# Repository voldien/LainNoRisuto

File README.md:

# LainNoRisuto

Just a collection of electronic schematic and board layouts.

## ARM ToolChain

```bash
```

## AVR ToolChain

```bash
sudo apt-get install gcc-avr binutils-avr avr-libc gdb-avr avrdude
```

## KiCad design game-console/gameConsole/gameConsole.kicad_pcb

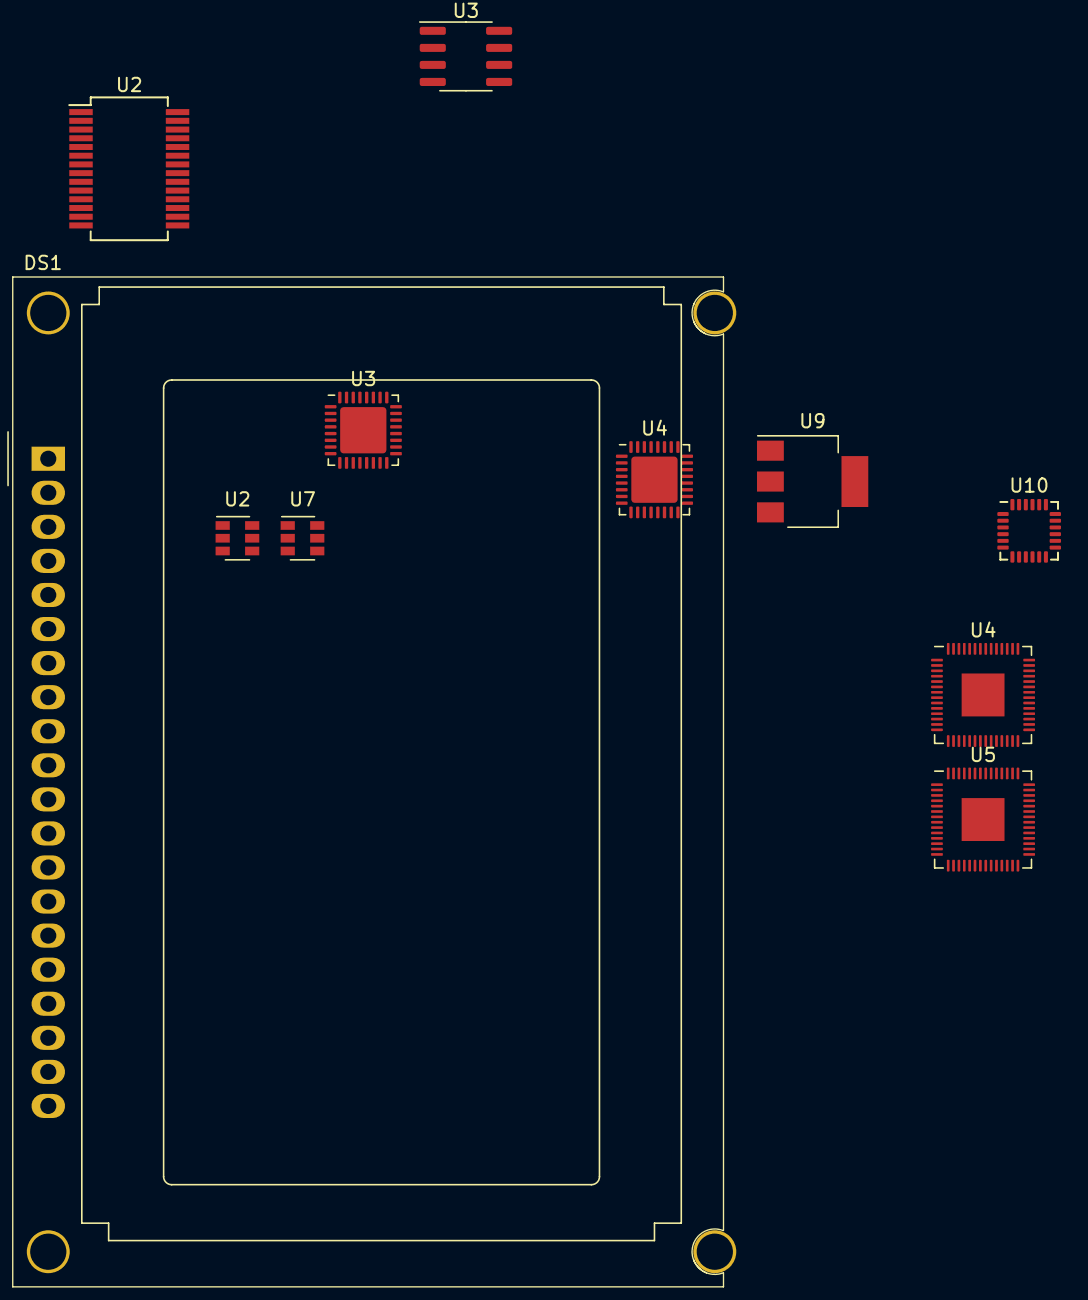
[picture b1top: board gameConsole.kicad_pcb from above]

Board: 2 copper layers, 11 parts (0 on the bottom side), 11 nets, no tracks yet.

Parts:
DS1: AG12864E
U2: AD1855; SSOP-28_5.3x10.2mm_P0.65mm
U2#2, U7: MCP4725xxx-xCH; SOT-23-6
U3, U4: CS43L21; QFN-32-1EP_5x5mm_P0.5mm_EP3.45x3.45mm
U3#2: DS1307Z+; SOIC-8_3.9x4.9mm_P1.27mm
U4#2, U5: RP2040; QFN-56-1EP_7x7mm_P0.4mm_EP3.2x3.2mm
U9: AP1117-33; SOT-223-3_TabPin2
U10: MPU-6050; InvenSense_QFN-24_4x4mm_P0.5mm

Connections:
+3.3V: U2#2.3 (VDD), U7.3 (VDD), U7.6 (A0), U10.13 (VDD)
GND: U2#2.2 (VSS), U2#2.6 (A0), U3#2.4 (GND), U7.2 (VSS), U10.18 (GND)
unnamed: U2.11, U2.15
unnamed: U3.13, U3.33
unnamed: U4#2.23 (DVDD), U4#2.50 (DVDD)
unnamed: U4#2.1 (IOVDD), U4#2.10 (IOVDD), U4#2.22 (IOVDD), U4#2.33 (IOVDD), U4#2.42 (IOVDD), U4#2.49 (IOVDD)
unnamed: U4.13, U4.33
unnamed: U5.23 (DVDD), U5.50 (DVDD)
unnamed: U5.1 (IOVDD), U5.10 (IOVDD), U5.22 (IOVDD), U5.33 (IOVDD), U5.42 (IOVDD), U5.49 (IOVDD)
SCL: U2#2.5 (SCL), U3#2.6 (SCL), U10.23 (SCL)
SDA: U2#2.4 (SDA), U3#2.5 (SDA), U10.24 (SDA)

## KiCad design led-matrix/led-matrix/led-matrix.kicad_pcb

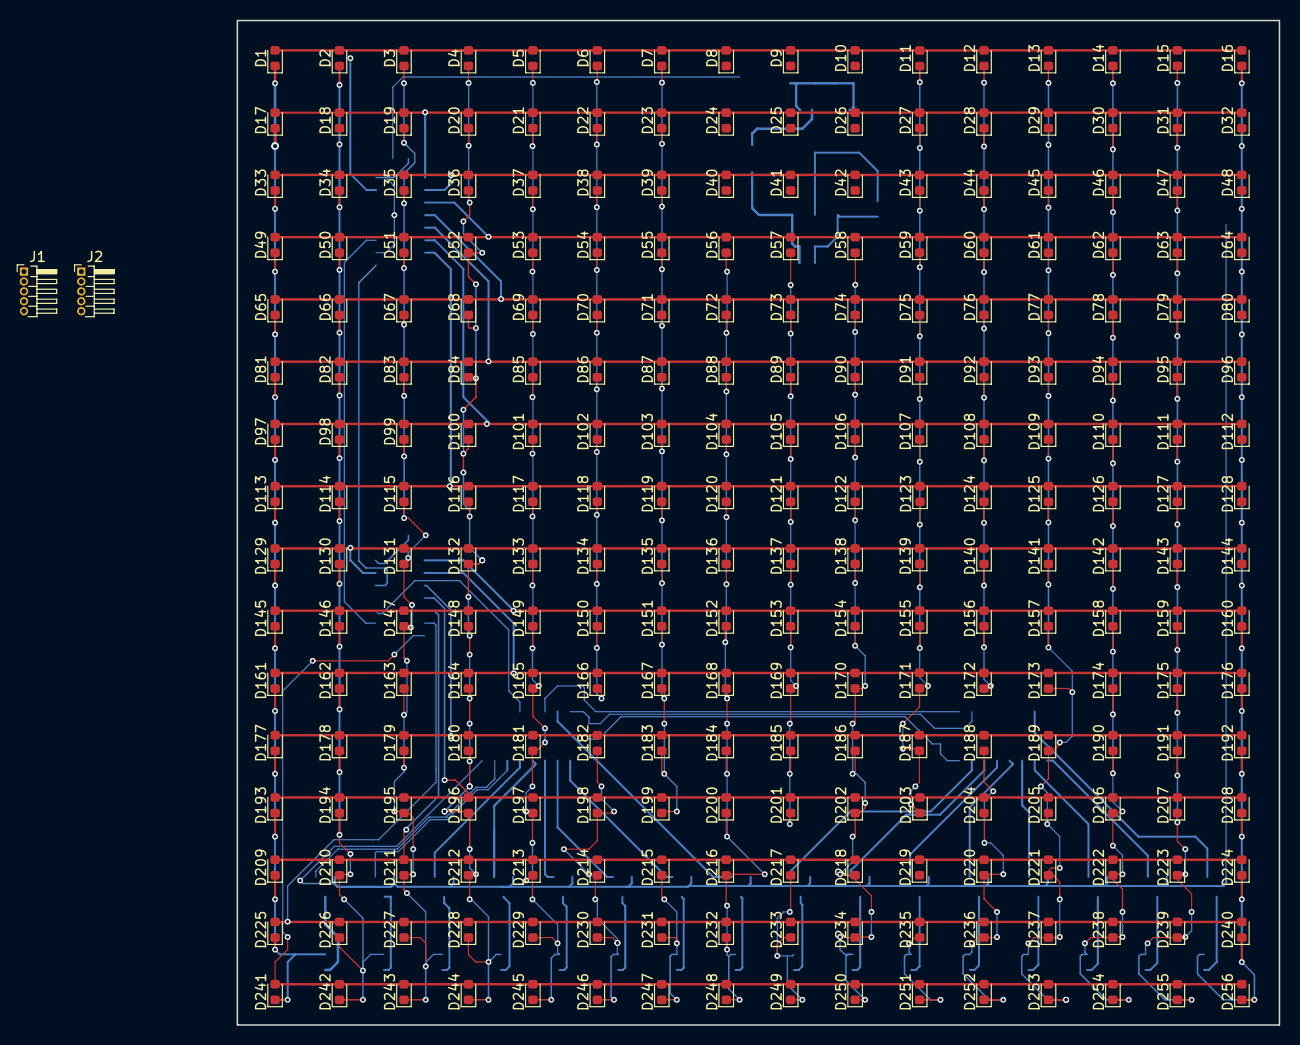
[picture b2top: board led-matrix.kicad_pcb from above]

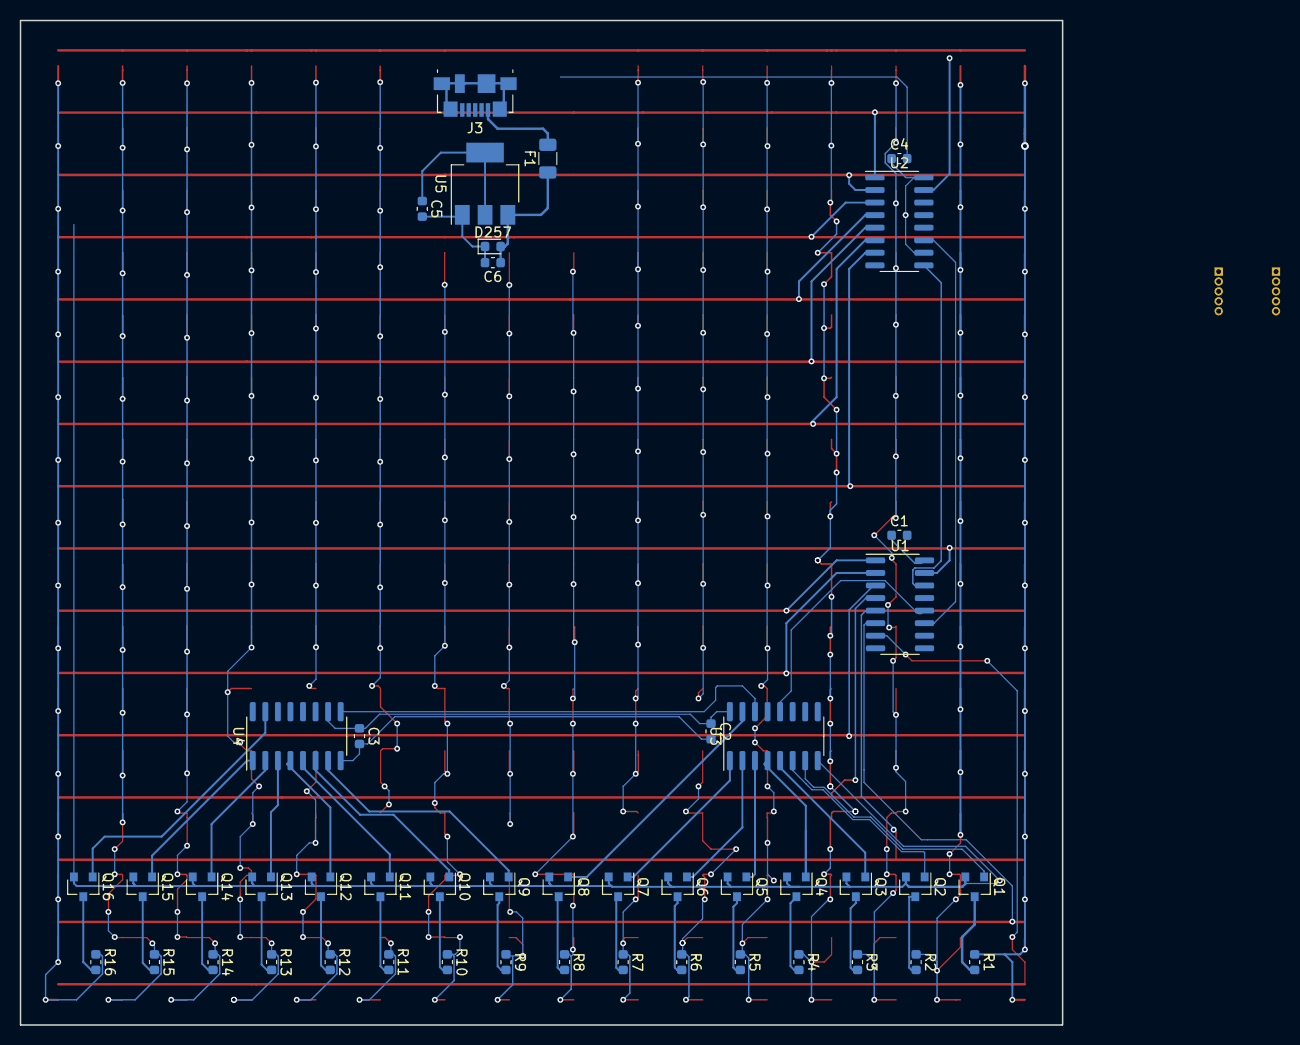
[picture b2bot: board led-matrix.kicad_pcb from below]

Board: 2 copper layers, 105.4 x 101.6 mm, 304 parts (46 on the bottom side), 77 nets.

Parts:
C1, C2, C3, C4, C5, C6: C; C_0603_1608Metric
D1, D2, D3, D4, D5, D6, D7, D8, D9, D10, D11, D12, D13, D14, D15, D16, D17, D18, D19, D20, D21, D22, D23, D24, D25, D26, D27, D28, D29, D30, D31, D32, D33, D34, D35, D36, D37, D38, D39, D40, D41, D42, D43, D44, D45, D46, D47, D48, D49, D50, D51, D52, D53, D54, D55, D56, D57, D58, D59, D60, D61, D62, D63, D64, D65, D66, D67, D68, D69, D70, D71, D72, D73, D74, D75, D76, D77, D78, D79, D80, D81, D82, D83, D84, D85, D86, D87, D88, D89, D90, D91, D92, D93, D94, D95, D96, D97, D98, D99, D100, D101, D102, D103, D104, D105, D106, D107, D108, D109, D110, D111, D112, D113, D114, D115, D116, D117, D118, D119, D120, D121, D122, D123, D124, D125, D126, D127, D128, D129, D130, D131, D132, D133, D134, D135, D136, D137, D138, D139, D140, D141, D142, D143, D144, D145, D146, D147, D148, D149, D150, D151, D152, D153, D154, D155, D156, D157, D158, D159, D160, D161, D162, D163, D164, D165, D166, D167, D168, D169, D170, D171, D172, D173, D174, D175, D176, D177, D178, D179, D180, D181, D182, D183, D184, D185, D186, D187, D188, D189, D190, D191, D192, D193, D194, D195, D196, D197, D198, D199, D200, D201, D202, D203, D204, D205, D206, D207, D208, D209, D210, D211, D212, D213, D214, D215, D216, D217, D218, D219, D220, D221, D222, D223, D224, D225, D226, D227, D228, D229, D230, D231, D232, D233, D234, D235, D236, D237, D238, D239, D240, D241, D242, D243, D244, D245, D246, D247, D248, D249, D250, D251, D252, D253, D254, D255, D256: LED; LED_0603_1608Metric
D257: D_Zener; D_0603_1608Metric
F1: Polyfuse; Fuse_1206_3216Metric
J1, J2: Conn_2Rows-05Pins; PinHeader_1x05_P1.00mm_Horizontal
J3: USB_B_Micro; USB_Micro-B_Molex_47346-0001
Q1, Q2, Q3, Q4, Q5, Q6, Q7, Q8, Q9, Q10, Q11, Q12, Q13, Q14, Q15, Q16: 2N7002; SOT-23
R1, R2, R3, R4, R5, R6, R7, R8, R9, R10, R11, R12, R13, R14, R15, R16: R_US; R_0603_1608Metric
U1, U2, U3, U4: 74LS595; SOIC-16_3.9x9.9mm_P1.27mm
U5: AMS1117-3.3; SOT-223-3_TabPin2

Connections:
+5V: F1.2, J3.1
CLR: J1.4, J2.4, U1.12, U2.12, U3.12, U4.12
COL0: Q16.1, U4.15
COL1: Q15.1, U4.1
COL2: Q14.1, U4.2
COL3: Q13.1, U4.3
COL4: Q12.1, U4.4
COL5: Q11.1, U4.5
COL6: Q10.1, U4.6
COL7: Q9.1, U4.7
COL8: Q8.1, U3.15
COL9: Q7.1, U3.1
COL10: Q6.1, U3.2
COL11: Q5.1, U3.3
COL12: Q4.1, U3.4
COL13: Q3.1, U3.5
COL14: Q2.1, U3.6
COL15: Q1.1, U3.7
COLNEXT: J1.1, U3.9
COLSEQ: U3.14, U4.9
DRIVE0: Q16.3, R16.2
DRIVE1: Q15.3, R15.2
DRIVE2: Q14.3, R14.2
DRIVE3: Q13.3, R13.2
DRIVE4: Q12.3, R12.2
DRIVE5: Q11.3, R11.2
DRIVE6: Q10.3, R10.2
DRIVE7: Q9.3, R9.2
DRIVE8: Q8.3, R8.2
DRIVE9: Q7.3, R7.2
DRIVE10: Q6.3, R6.2
DRIVE11: Q5.3, R5.2
DRIVE12: Q4.3, R4.2
DRIVE13: Q3.3, R3.2
DRIVE14: Q2.3, R2.2
DRIVE15: Q1.3, R1.2
GND: C1.2, C2.2, C3.2, C4.2, C5.2, C6.2, D257.1, J3.5, Q1.2, Q2.2, Q3.2, Q4.2, Q5.2, Q6.2, Q7.2, Q8.2, Q9.2, Q10.2, Q11.2, Q12.2, Q13.2, Q14.2, Q15.2, Q16.2, U1.8, U2.8, U3.8, U4.8, U5.1
unnamed: C6.1, D257.2, F1.1, U5.3
unnamed: D1.1, D17.1, D33.1, D49.1, D65.1, D81.1, D97.1, D113.1, D129.1, D145.1, D161.1, D177.1, D193.1, D209.1, D225.1, D241.1, R1.1
unnamed: D10.1, D26.1, D42.1, D58.1, D74.1, D90.1, D106.1, D122.1, D138.1, D154.1, D170.1, D186.1, D202.1, D218.1, D234.1, D250.1, R10.1
unnamed: D4.1, D20.1, D36.1, D52.1, D68.1, D84.1, D100.1, D116.1, D132.1, D148.1, D164.1, D180.1, D196.1, D212.1, D228.1, D244.1, R4.1
unnamed: D5.1, D21.1, D37.1, D53.1, D69.1, D85.1, D101.1, D117.1, D133.1, D149.1, D165.1, D181.1, D197.1, D213.1, D229.1, D245.1, R5.1
unnamed: D6.1, D22.1, D38.1, D54.1, D70.1, D86.1, D102.1, D118.1, D134.1, D150.1, D166.1, D182.1, D198.1, D214.1, D230.1, D246.1, R6.1
unnamed: D7.1, D23.1, D39.1, D55.1, D71.1, D87.1, D103.1, D119.1, D135.1, D151.1, D167.1, D183.1, D199.1, D215.1, D231.1, D247.1, R7.1
unnamed: D8.1, D24.1, D40.1, D56.1, D72.1, D88.1, D104.1, D120.1, D136.1, D152.1, D168.1, D184.1, D200.1, D216.1, D232.1, D248.1, R8.1
unnamed: D9.1, D25.1, D41.1, D57.1, D73.1, D89.1, D105.1, D121.1, D137.1, D153.1, D169.1, D185.1, D201.1, D217.1, D233.1, D249.1, R9.1
unnamed: D11.1, D27.1, D43.1, D59.1, D75.1, D91.1, D107.1, D123.1, D139.1, D155.1, D171.1, D187.1, D203.1, D219.1, D235.1, D251.1, R11.1
unnamed: D12.1, D28.1, D44.1, D60.1, D76.1, D92.1, D108.1, D124.1, D140.1, D156.1, D172.1, D188.1, D204.1, D220.1, D236.1, D252.1, R12.1
unnamed: D13.1, D29.1, D45.1, D61.1, D77.1, D93.1, D109.1, D125.1, D141.1, D157.1, D173.1, D189.1, D205.1, D221.1, D237.1, D253.1, R13.1
unnamed: D14.1, D30.1, D46.1, D62.1, D78.1, D94.1, D110.1, D126.1, D142.1, D158.1, D174.1, D190.1, D206.1, D222.1, D238.1, D254.1, R14.1
unnamed: D15.1, D31.1, D47.1, D63.1, D79.1, D95.1, D111.1, D127.1, D143.1, D159.1, D175.1, D191.1, D207.1, D223.1, D239.1, D255.1, R15.1
unnamed: D16.1, D32.1, D48.1, D64.1, D80.1, D96.1, D112.1, D128.1, D144.1, D160.1, D176.1, D192.1, D208.1, D224.1, D240.1, D256.1, R16.1
unnamed: D2.1, D18.1, D34.1, D50.1, D66.1, D82.1, D98.1, D114.1, D130.1, D146.1, D162.1, D178.1, D194.1, D210.1, D226.1, D242.1, R2.1
unnamed: D3.1, D19.1, D35.1, D51.1, D67.1, D83.1, D99.1, D115.1, D131.1, D147.1, D163.1, D179.1, D195.1, D211.1, D227.1, D243.1, R3.1
OE: J1.2, J2.2, U1.13, U2.13, U3.13, U4.13
ROW0: D1.2, D2.2, D3.2, D4.2, D5.2, D6.2, D7.2, D8.2, D9.2, D10.2, D11.2, D12.2, D13.2, D14.2, D15.2, D16.2, U2.15
ROW1: D17.2, D18.2, D19.2, D20.2, D21.2, D22.2, D23.2, D24.2, D25.2, D26.2, D27.2, D28.2, D29.2, D30.2, D31.2, D32.2, U2.1
ROW2: D33.2, D34.2, D35.2, D36.2, D37.2, D38.2, D39.2, D40.2, D41.2, D42.2, D43.2, D44.2, D45.2, D46.2, D47.2, D48.2, U2.2
ROW3: D49.2, D50.2, D51.2, D52.2, D53.2, D54.2, D55.2, D56.2, D57.2, D58.2, D59.2, D60.2, D61.2, D62.2, D63.2, D64.2, U2.3
ROW4: D65.2, D66.2, D67.2, D68.2, D69.2, D70.2, D71.2, D72.2, D73.2, D74.2, D75.2, D76.2, D77.2, D78.2, D79.2, D80.2, U2.4
ROW5: D81.2, D82.2, D83.2, D84.2, D85.2, D86.2, D87.2, D88.2, D89.2, D90.2, D91.2, D92.2, D93.2, D94.2, D95.2, D96.2, U2.5
ROW6: D97.2, D98.2, D99.2, D100.2, D101.2, D102.2, D103.2, D104.2, D105.2, D106.2, D107.2, D108.2, D109.2, D110.2, D111.2, D112.2, U2.6
ROW7: D113.2, D114.2, D115.2, D116.2, D117.2, D118.2, D119.2, D120.2, D121.2, D122.2, D123.2, D124.2, D125.2, D126.2, D127.2, D128.2, U2.7
ROW8: D129.2, D130.2, D131.2, D132.2, D133.2, D134.2, D135.2, D136.2, D137.2, D138.2, D139.2, D140.2, D141.2, D142.2, D143.2, D144.2, U1.15
ROW9: D145.2, D146.2, D147.2, D148.2, D149.2, D150.2, D151.2, D152.2, D153.2, D154.2, D155.2, D156.2, D157.2, D158.2, D159.2, D160.2, U1.1
ROW10: D161.2, D162.2, D163.2, D164.2, D165.2, D166.2, D167.2, D168.2, D169.2, D170.2, D171.2, D172.2, D173.2, D174.2, D175.2, D176.2, U1.2
ROW11: D177.2, D178.2, D179.2, D180.2, D181.2, D182.2, D183.2, D184.2, D185.2, D186.2, D187.2, D188.2, D189.2, D190.2, D191.2, D192.2, U1.3
ROW12: D193.2, D194.2, D195.2, D196.2, D197.2, D198.2, D199.2, D200.2, D201.2, D202.2, D203.2, D204.2, D205.2, D206.2, D207.2, D208.2, U1.4
ROW13: D209.2, D210.2, D211.2, D212.2, D213.2, D214.2, D215.2, D216.2, D217.2, D218.2, D219.2, D220.2, D221.2, D222.2, D223.2, D224.2, U1.5
ROW14: D225.2, D226.2, D227.2, D228.2, D229.2, D230.2, D231.2, D232.2, D233.2, D234.2, D235.2, D236.2, D237.2, D238.2, D239.2, D240.2, U1.6
ROW15: D241.2, D242.2, D243.2, D244.2, D245.2, D246.2, D247.2, D248.2, D249.2, D250.2, D251.2, D252.2, D253.2, D254.2, D255.2, D256.2, U1.7
ROWNEXT: J1.3, U1.9
ROWSEQ: U1.14, U2.9
SCK: J1.5, J2.5, U1.11, U2.11, U3.11, U4.11
SERCOL: J2.1, U4.14
SERROW: J2.3, U2.14
VCC: C1.1, C2.1, C3.1, C4.1, C5.1, U1.10, U1.16, U2.10, U2.16, U3.10, U3.16, U4.10, U4.16, U5.2

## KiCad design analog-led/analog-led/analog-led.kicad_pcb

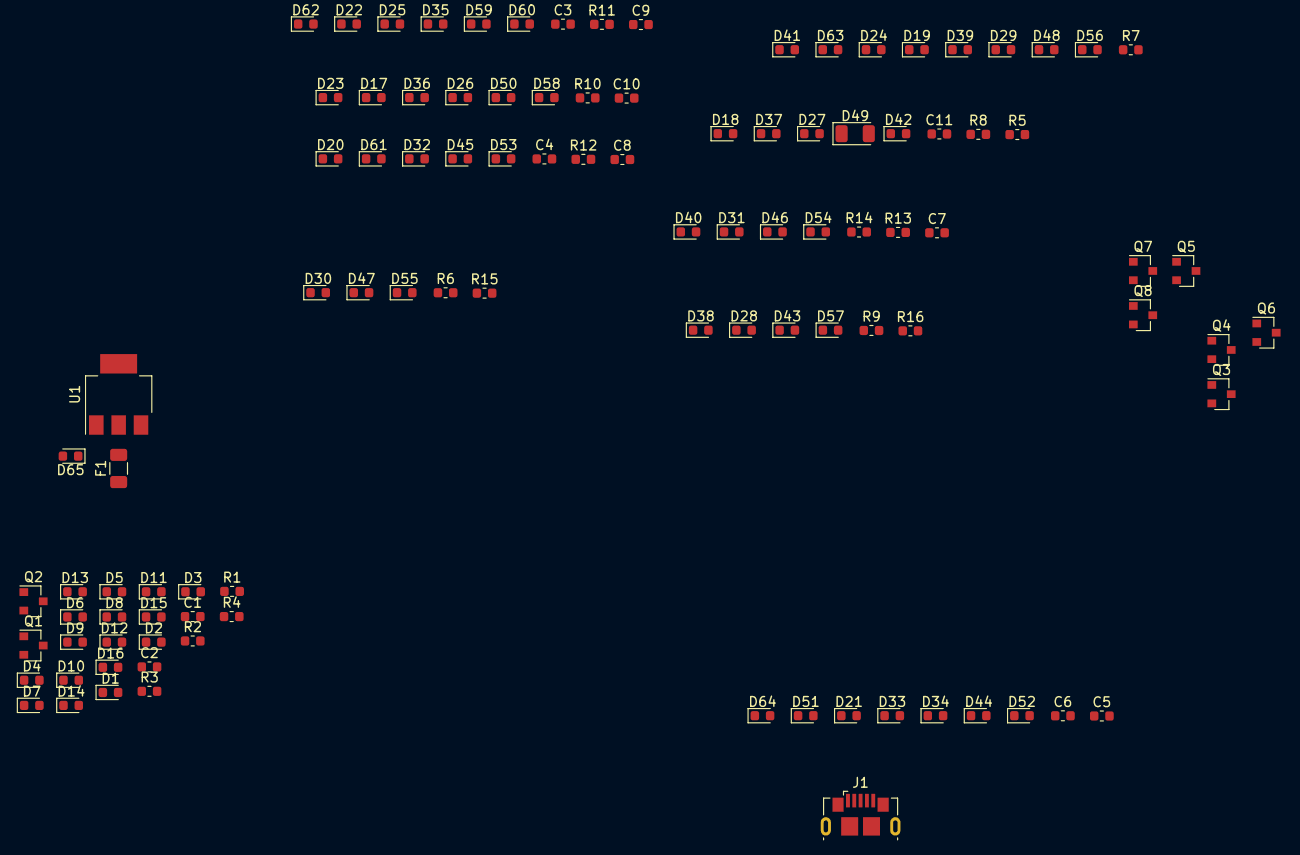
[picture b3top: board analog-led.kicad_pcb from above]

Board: 2 copper layers, 103 parts (0 on the bottom side), 28 nets, no tracks yet.

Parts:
C1, C2, C3, C4, C5, C6, C7, C8, C9, C10, C11: C_Small; C_0603_1608Metric
D1, D2, D3, D4, D5, D6, D7, D8, D9, D10, D11, D12, D13, D14, D15, D16, D17, D18, D19, D20, D21, D22, D23, D24, D25, D26, D27, D28, D29, D30, D31, D32, D33, D34, D35, D36, D37, D38, D39, D40, D41, D42, D43, D44, D45, D46, D47, D48, D50, D51, D52, D53, D54, D55, D56, D57, D58, D59, D60, D61, D62, D63, D64: LED; D_0603_1608Metric
D49: LED; D_1206_3216Metric
D65: D_Zener; D_0603_1608Metric
F1: Fuse; Fuse_1206_3216Metric
J1: USB_B_Micro; USB_Micro-B_GCT_USB3076-30-A
Q1, Q2, Q3, Q4, Q5, Q6, Q7, Q8: BC547; SOT-23
R1, R2, R3, R4, R5, R6, R7, R8, R9, R10, R11, R12, R13, R15, R16: R_Small_US; R_0603_1608Metric
R14: 22K; R_0603_1608Metric
U1: AZ1117-3.3; SOT-223

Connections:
+3V3: C9.2, C10.2, Q1.2, R1.1, R2.1, R3.1, R4.1, R5.1, R6.1, R7.1, R8.1, R9.1, R10.1, R11.1, R12.1, R13.1, R14.1, R15.1, R16.1, U1.3
+5V: F1.1, J1.1
GND: C9.1, C10.1, C11.1, D65.2, J1.5, Q1.3, Q2.3, Q3.3, Q4.3, Q5.3, Q6.3, Q7.3, Q8.3, U1.1
unnamed: C1.1, D1.1, D2.1, D3.1, D4.1, D5.1, D6.1, D7.1, D8.1, Q1.1
unnamed: C1.2, Q2.2, R2.2
unnamed: C2.1, D9.1, D10.1, D11.1, D12.1, D13.1, D14.1, D15.1, D16.1, Q2.1
unnamed: C2.2, Q3.2, R4.2
unnamed: C3.1, D17.1, D18.1, D19.1, D20.1, D21.1, D22.1, D23.1, D24.1, Q3.1
unnamed: C3.2, Q4.2, R6.2
unnamed: C4.1, D25.1, D26.1, D27.1, D28.1, D29.1, D30.1, D31.1, D32.1, Q4.1
unnamed: C4.2, Q5.2, R8.2
unnamed: C5.1, D33.1, D34.1, D35.1, D36.1, D37.1, D38.1, D39.1, D40.1, Q5.1
unnamed: C5.2, Q6.2, R10.2
unnamed: C6.1, D41.1, D42.1, D43.1, D44.1, D45.1, D46.1, D47.1, D48.1, Q6.1
unnamed: C6.2, Q7.2, R12.2
unnamed: C7.1, D49.1, D50.1, D51.1, D52.1, D53.1, D54.1, D55.1, D56.1, Q7.1
unnamed: C7.2, Q8.2, R14.2
unnamed: C8.1, D57.1, D58.1, D59.1, D60.1, D61.1, D62.1, D63.1, D64.1, Q8.1
unnamed: C8.2, R16.2
unnamed: C11.2, D65.1, F1.2, U1.2
unnamed: D1.2, D2.2, D3.2, D4.2, D5.2, D6.2, D7.2, D8.2, R1.2
unnamed: D9.2, D10.2, D11.2, D12.2, D13.2, D14.2, D15.2, D16.2, R3.2
unnamed: D17.2, D18.2, D19.2, D20.2, D21.2, D22.2, D23.2, D24.2, R5.2
unnamed: D25.2, D26.2, D27.2, D28.2, D29.2, D30.2, D31.2, D32.2, R7.2
unnamed: D33.2, D34.2, D35.2, D36.2, D37.2, D38.2, D39.2, D40.2, R9.2
unnamed: D41.2, D42.2, D43.2, D44.2, D45.2, D46.2, D47.2, D48.2, R11.2
unnamed: D49.2, D50.2, D51.2, D52.2, D53.2, D54.2, D55.2, D56.2, R13.2
unnamed: D57.2, D58.2, D59.2, D60.2, D61.2, D62.2, D63.2, D64.2, R15.2

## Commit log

2021-05-01 Config files
2021-05-01 Added tiny blink init source code
2021-05-01 Added init christmas card source code
2021-05-01 Added christmas schematic and pcb board
2021-05-01 Added atdb
2021-05-01 atdb pcb and schematic
2021-05-01 Added schematic and board
2021-05-01 Added root cmake
2021-05-01 Added
2021-05-01 Added readme and license file
2021-05-01 Add more source files
2021-05-01 Addded cmake module for handle avr-gcc with CMake
2021-05-01 Added gerber files
2021-05-01 Added schematic and board layout
2021-05-01 Added image of atdb
2021-05-02 Added layout
2021-05-03 Clock init souce files
2021-05-03 init source files
2021-05-12 Added board layout
2021-05-12 Minor update
2021-05-12 Init readme
2021-08-14 Minor
2021-08-31 Added init LED matrix
2021-09-01 Updated schematic
2021-09-03 Improved annotations and board layout
2021-09-04 Updated layout
2021-09-04 Updated layout grid
2021-09-04 Setup LED matrix
2021-09-05 Updated schematic and layout
2021-09-17 Updated minor
2021-12-22 Init
2022-01-06 Improved layout and schematic
2022-01-06 Init game console design
2022-04-12 Code formated
2023-01-20 Added init christmas card version 2.0
2023-04-06 Added init christmas card version 2 schematic and layout
2023-04-06 removed, replaced
2023-04-06 Added init source code, copied from the christmas card V1
2023-04-06 Added init source code for LED Clock matrix
2023-04-07 Added readme and removed file
2023-05-29 Added kicad git ignore
2023-05-29 Added init kicad source files
2023-05-29 Added init WIP game console firmware code
2023-05-30 Minor improvements
2025-05-21 Improved logic and other changes
2025-05-21 Updated git ignore
2025-05-21 Added AVR cmake config file
2025-05-21 Improved signal and other minor improvements
2025-05-22 Added pin interrupt, timer overflow interrupt and other changes and improvements
2025-05-22 Improvement and other changes
2025-05-23 Improved push button and other changes
2025-05-24 Improved code and minor doc
2025-05-24 Updated schematic and board layout
2025-05-25 Fixed RCLK trace missing issue
2025-05-28 Relocated files, removed unused files, updated christmas and clock board and other changes
2025-06-08 Init source code
2025-06-11 Improvement and changes
2025-06-11 Code cleanup and other changes
2025-07-05 Minor board fixes and other changes
2025-07-21 Removed unused files, update board, code and other changes
2025-07-29 Added LED Matrix
2025-07-31 Minor fixes and cleanup
2025-08-07 Fixed clock prescalar, and minor fixes
2025-08-14 Improvement, fixes and other changes
2026-01-05 Relocated files and minor changes
2026-01-31 Updated Gerber
